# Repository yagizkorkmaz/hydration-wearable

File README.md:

# Hydration Monitoring Wearable

A wrist-worn sensor node and companion iOS app for non-invasive hydration monitoring. An ESP32-S3 samples skin conductance (GSR), optical PPG (red + IR), skin temperature and humidity and streams them over Bluetooth Low Energy. The iPhone app logs the data, estimates heart rate from the PPG signal and classifies water need (low / moderate / high) with a k-NN model.

Graduation project, Istanbul Bilgi University, B.Sc. Electrical and Electronics Engineering, 2026. This is a research prototype, not a medical device.

*The prototype: hand-wired on perfboard, worn on the wrist, with the GSR electrodes on two fingers.*

## How it works

```
GSR electrodes ──(analog)──┐
MAX30102 PPG ───(I2C)──────┤
SHT31 temp/humidity (I2C)──┼── ESP32-S3 ──(BLE notify, 5 Hz)──> iOS app
SSD1315 OLED <──(I2C)──────┘                                     ├─ CSV logging
                                                                 ├─ heart rate (PPG periodogram)
                                                                 └─ water-need class + index (k-NN)
```

The ESP32-S3 samples all sensors in a non-blocking loop, shows live values on the OLED, and sends one CSV packet every 200 ms to a connected phone. All signal processing and classification currently run in the app.

## Hardware

There are two hardware stages in this repository: the working prototype that the firmware runs on, and a PCB design that integrates the same circuit on one board.

### Working prototype

Hand-wired on perfboard with an ESP32-S3 board and sensor modules.

| Part | Role | Interface | Pin / address |
|---|---|---|---|
| ESP32-S3 | MCU, BLE radio | – | – |
| MAX30102 | PPG, red + IR | I2C | 0x57 |
| SHT31 | Temperature, humidity | I2C | 0x44 or 0x45 |
| GSR front end | Skin conductance | ADC, 12-bit | GPIO4 |
| SSD1315 OLED, 128x64 | Live readout | I2C | 0x3C or 0x3D |

I2C bus: SDA on GPIO8, SCL on GPIO9, 400 kHz.

### PCB design

KiCad 10 project in `hardware/` (`bitirme2.kicad_pro`, schematic and board). The board was fabricated and partially assembled.

*The fabricated board with the SHT30, MPU-6050, LM324 and passives soldered. The ESP32-C3 module, the trimmer and the connectors are not fitted in this photo.*

| Item | Value |
|---|---|
| Board | 57 × 39 mm, 2 copper layers, 1.6 mm |
| Routing | 0.2 mm tracks on the top layer, ground pour on the bottom layer |
| Components | 32, all on the top side, 0603 passives |
| MCU | ESP32-C3 SuperMini module on through-hole headers |
| GSR front end | LM324 op-amp stage with a 200 kΩ trimmer, electrode input on a 2-pin connector, output on GPIO4 |
| On-board sensors | SHT30 temperature/humidity (I2C 0x44), MPU-6050 IMU (I2C 0x68) |
| I2C | SDA on GPIO8, SCL on GPIO9, 4.7 kΩ pull-ups |
| Test points | SDA, SCL, VCC, GND |

The GSR front end follows the Seeed Studio Grove GSR sensor circuit. The pin assignment (GPIO4, GPIO8, GPIO9) is the same as in the firmware, so the firmware can be moved between the two boards without changing pins.

Differences from the working prototype:

- The PCB is designed around the ESP32-C3 SuperMini; the prototype and the firmware in this repository use an ESP32-S3.
- The PCB adds an MPU-6050 for motion sensing. The current firmware does not read it yet.
- The MAX30102 and the OLED are not on the PCB; they connect as external modules on the I2C bus.

Known issues in the board file:

- The ground pads of the surface-mount parts are not connected. The ground pour is on the bottom layer and the board has no vias, so only the through-hole ground pins reach it. A revision needs a ground pour on the top layer or vias next to the ground pads.
- The SCL test point is not routed.

## Firmware

Written in C++ on the Arduino-ESP32 core. Source: `firmware/hydration_sensor/hydration_sensor.ino`.

**Sensor acquisition**

- MAX30102 runs in red + IR mode at 100 Hz with 4-sample averaging, 411 µs pulse width. The FIFO is drained every loop iteration.
- SHT31 is read once per second.
- GSR is read through the 12-bit ADC every loop iteration.
- OLED refreshes every 200 ms and shows each sensor value plus BLE connection state.

**BLE interface**

| Item | Value |
|---|---|
| Device name | `HydrationSensor` |
| Service UUID | `6E400001-B5A3-F393-E0A9-E50E24DCCA9E` (Nordic UART Service) |
| TX characteristic | `6E400003-B5A3-F393-E0A9-E50E24DCCA9E` (notify, read) |
| MTU | 100 |
| Update rate | 5 Hz |

Packet format, plain-text CSV:

```
timestamp,gsr,red,ir,temp,humidity
15240,1874,84231,91342,24.63,46.18
```

`timestamp` is milliseconds since boot, `gsr` is the raw ADC count (0–4095), `red` and `ir` are raw MAX30102 counts, `temp` is in °C and `humidity` in %RH. Streaming is one-way; besides the iOS app, any client that speaks Nordic UART (for example nRF Connect) can read it.

**Fault tolerance**

- BLE is initialised before any sensor, so the device still advertises if a sensor is missing or the I2C bus is faulty.
- The I2C bus is scanned at boot and each sensor is probed separately; a missing sensor is reported on serial and on the OLED as `ERR` instead of stopping the firmware.
- I2C calls have a 50 ms timeout so a wiring fault cannot hang the loop.
- After a disconnect, advertising is restarted from the main loop (not from the BLE callback), and re-triggered every 10 s while no phone is connected.
- While disconnected, a status line is printed on serial every 5 s.

## Water-need model

A standardized, distance-weighted k-nearest-neighbour classifier (k = 3) with three classes: LOW, MODERATE and HIGH water need.

**Input.** One 60-second window of the 5 Hz stream (300 samples), reduced to 8 features:

```
gsr_mean, gsr_sd, gsr_slope, red_mean, red_sd, ir_mean, ir_sd, red_ir_ratio
```

**Steps.**

1. Each feature is z-scored with the training mean and standard deviation.
2. The 3 nearest training windows are found by squared Euclidean distance.
3. Each neighbour votes with weight `1 / (d² + 0.001)`; the normalised votes are the class weights.
4. Water Need Index: `WNI = 100 × (0.5 · P(MODERATE) + 1.0 · P(HIGH))`, from 0 to 100.
5. A confidence value is the winning class weight scaled down by the distance to the nearest training window, so readings unlike the training data do not look certain.

**Training data and limits.** The model holds 94 training windows (55 LOW, 14 MODERATE, 25 HIGH). Labels are weak experimental labels taken from selected recording intervals of a single session on 17 August 2026. They are not biochemical or clinical dehydration labels, so the output is a relative indicator from a small data set and has not been validated against a reference measurement.

**Two copies of the same model.**

- `model/hydration_model.h` – C header with the model constants and a `predictHydration()` function, written for on-device inference on the ESP32.
- `app/HydrationLogger/HydrationModel.swift` – the same constants and algorithm in Swift, used by the app.

The current firmware does not call the C version yet; inference runs on the phone.

The training script and the recorded sessions are not included in this repository.

## iOS app (Hydration Logger)

Native iOS app in Swift, using SwiftUI and CoreBluetooth, targeting iOS 17 and later. Source: `app/`.

**Screens**

- **Live** – water-need class, WNI gauge and heart rate, followed by estimated blood pressure, GSR, red, IR, perfusion index, temperature, humidity and the class weights. A progress bar is shown until the 60 s model window is at least 80 % full.
- **Recordings** – start/stop, connection state, the raw packet stream, and the list of recorded CSV files with share and delete.

Interface text is partly in Turkish.

**Heart rate**

The PPG signal reaches the phone at 5 Hz, which gives only 3–4 samples per beat, so beats are not counted in the time domain. Instead:

1. The last 30 s of the IR channel is resampled onto a uniform 5 Hz grid by linear interpolation, to absorb BLE jitter and dropped packets.
2. Baseline drift is removed by subtracting a 2 s moving average.
3. A Hann window is applied and a fine-step periodogram is evaluated between 0.7 and 2.2 Hz (42–132 bpm); the strongest peak is the heart rate, with about 2 bpm resolution.
4. A quality score measures how dominant the peak is. Below 0.35 the value is hidden. If the mean IR level is under 20,000 the sensor is treated as not in contact with skin.
5. The displayed value is smoothed exponentially.

The upper limit is kept at 132 bpm because Nyquist at 5 Hz is 150 bpm and the firmware forwards only the latest FIFO sample, so higher frequencies alias.

**Perfusion index.** AC amplitude (5th to 95th percentile of the detrended IR signal) divided by the DC level, in percent.

**Blood pressure (estimate only).** Blood pressure cannot be measured with a single PPG channel. The value shown in the app is a heuristic, labelled as an estimate: a baseline entered by the user from a cuff reading (default 120/80 mmHg at 70 bpm) is shifted by the change in heart rate and by the drop in perfusion index relative to the first 60 s of the session, then clipped to physiological limits. It does not replace a cuff measurement.

**Recorded data**

Two files per connection in the app's `Documents/` folder, also visible in the iOS Files app and in Finder:

- `<date>_<time>_hydration.csv` – every raw packet with the phone's receive time:

  ```
  received_at,esp_millis,gsr,red,ir,temperature,humidity
  2026-08-14T17:30:05.412+03:00,12480,2014,80235,90512,24.51,45.32
  ```

- `<date>_<time>_vitals.csv` – derived values, one row per second: heart rate and quality, estimated blood pressure, perfusion index, class, WNI, confidence, nearest-neighbour distance, class weights, and the 8 model features.

Unexpected binary payloads are written as hex (`0x...`) instead of being dropped.

**Reliability**

- Writes are buffered and flushed at least every 2 s, when 4 KB has accumulated, when the app goes to the background and when the connection drops.
- Recording continues with the screen locked or the app in the background (`bluetooth-central` background mode).
- CoreBluetooth state restoration is enabled, so if iOS terminates the app under memory pressure it is relaunched in the background and the connection resumes.
- If the link drops, the app keeps trying to reconnect and starts new session files when the device comes back. If the ESP32 reboots (its millisecond counter goes backwards), the processing window is cleared so old and new data are not mixed.
- Limitation: if the app is force-quit from the app switcher, iOS does not relaunch it and recording stops.

**Source files**

| File | Role |
|---|---|
| `BLEManager.swift` | Scanning, connecting, automatic reconnect, notify subscription, packet parsing, background restoration |
| `DataLogger.swift` | Session files, buffered writes, listing and deleting files |
| `VitalsEngine.swift` | Sliding windows, the 8 model features, heart rate, perfusion index, blood pressure estimate |
| `HydrationModel.swift` | k-NN classifier, Swift copy of `model/hydration_model.h` |
| `DashboardView.swift` | Live screen and blood pressure calibration |
| `ContentView.swift` | Tabs and the recordings screen |

## Building

**Firmware**

1. Arduino IDE with the ESP32 board package. Board: **ESP32S3 Dev Module**.
2. Tools → **USB CDC On Boot: Enabled** (needed for serial output over the S3's native USB).
3. Install libraries: `U8g2`, `SparkFun MAX3010x Pulse and Proximity Sensor Library`, `Adafruit SHT31 Library`.
4. Open `firmware/hydration_sensor/hydration_sensor.ino`, upload, open the serial monitor at 115200 baud.

**iOS app**

1. Install [XcodeGen](https://github.com/yonaskolb/XcodeGen), then run `xcodegen generate` inside `app/` to create the Xcode project from `project.yml`.
2. Open `HydrationLogger.xcodeproj`, select your own team under Signing & Capabilities, and change the bundle identifier if it is taken.
3. Run on a physical iPhone or iPad. The simulator has no Bluetooth hardware.
4. Allow Bluetooth access on first launch, then start recording; the app finds `HydrationSensor` and connects automatically.

## Repository layout

```
firmware/hydration_sensor/   ESP32-S3 firmware
model/                       k-NN model as a C header
app/                         iOS app: project.yml and HydrationLogger/ sources
hardware/                    KiCad project: schematic and PCB layout
docs/                        photos
```

## Status and limitations

- Sensor acquisition, OLED, BLE streaming, CSV logging, heart rate and water-need classification run end to end on the bench.
- The water-need model is trained on 94 windows from one recording day with weak labels; it needs more subjects and a reference measurement before its output means anything beyond a relative trend.
- Classification runs in the app. Moving it onto the ESP32 with `model/hydration_model.h` is the next step.
- Deep sleep and the power button are disabled in this firmware build. An earlier build put the device to sleep shortly after boot when GPIO5 read low; GPIO5 is now only read for diagnostics.
- PPG is sampled at 100 Hz on the sensor but only the latest value is sent at 5 Hz, which limits heart rate to 132 bpm and rules out waveform analysis. Sending at 25 Hz or computing heart rate on the ESP32 would remove this limit.
- The PCB was fabricated and partially assembled, but the board file has open issues (see Hardware). The firmware and the recordings in this repository come from the perfboard prototype.

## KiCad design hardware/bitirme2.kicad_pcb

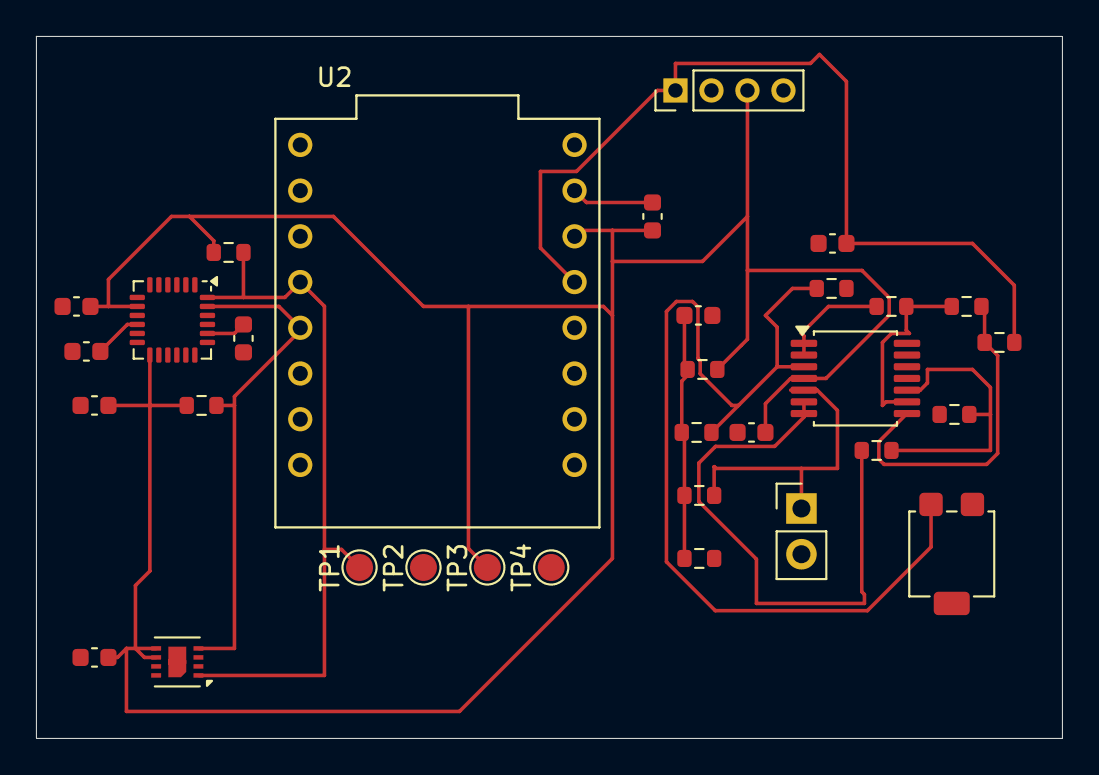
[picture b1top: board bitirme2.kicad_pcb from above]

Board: 2 copper layers, 57.0 x 39.0 mm, 32 parts (0 on the bottom side), 15 nets.

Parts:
C1, C2, C3, C4, C9: 100nF; C_0603_1608Metric
C5: 2.2nF; C_0603_1608Metric
C6, C7: 100n; C_0603_1608Metric
C8: 4.7µF; C_0603_1608Metric
J1: JST 2.0; PinHeader_1x02_P2.54mm_Vertical
J3: SMD Grove; PinHeader_1x04_P2.00mm_Vertical
R1: 200K; Potentiometer_Bourns_3314G_Vertical
R2, R7, R12, R13: 4.7K; R_0603_1608Metric
R3: DNP; R_0603_1608Metric
R4, R5, R6, R11: 200K; R_0603_1608Metric
R8, R10: 100k; R_0603_1608Metric
R9: 1M; R_0603_1608Metric
TP1, TP2, TP3, TP4: TestPoint; TestPoint_Pad_D1.5mm
U1: LM324PW-TSSOP14; TSSOP-14_4.4x5mm_P0.65mm
U2: ESP32_C3_Super_Mini; MODULE_ESP32-C3_SUPERMINI_TH
U3: SHT30-DIS; Sensirion_DFN-8-1EP_2.5x2.5mm_P0.5mm_EP1.1x1.7mm
U4: MPU-6050; InvenSense_QFN-24_4x4mm_P0.5mm

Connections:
/GND: C1.1, C2.1, C3.1, C4.2, C5.2, C6.2, C7.1, C8.1, C9.1, J1.2, J3.4, R1.2 (3), R3.2, R7.1, R11.1, TP4.1 (1_1), U1.11 (V-), U2.G, U3.2 (ADDR), U3.8 (VSS), U3.9 (VSS), U4.1 (CLKIN), U4.9 (AD0), U4.11 (FSYNC), U4.18 (GND)
/SCL: R13.2, TP2.1 (1_1), U2.9 (GPIO9), U3.4 (SCL), U4.23 (SCL)
/SDA: R12.2, TP1.1 (1_1), U2.8 (GPIO8), U3.1 (SDA), U4.24 (SDA)
/SIG: C2.2, J3.1, R9.2, U2.4 (GPIO4)
/VCC: C3.2, C6.1, C7.2, C8.2, C9.2, J3.3, R2.2, R12.1, R13.1, TP3.1 (1_1), U1.4 (V+), U2.3.3, U3.5 (VDD), U3.6 (~RESET), U4.8 (VLOGIC), U4.13 (VDD)
unnamed: C1.2, R2.1, R5.1, R6.1, R7.2
unnamed: J1.1, R6.2, U1.5 (IN+)
unnamed: R1.3 (2), R3.1, R5.2, U1.3 (IN+)
unnamed: R8.1, U1.1 (OUT), U1.2 (IN-)
unnamed: R10.2, R11.2, U1.10 (IN+)
unnamed: R4.1, R8.2, U1.9 (IN-)
unnamed: R4.2, R9.1, U1.8 (OUT)
unnamed: R10.1, U1.6 (IN-), U1.7 (OUT)
unnamed: C5.1, U4.20 (CPOUT)
unnamed: C4.1, U4.10 (REGOUT)
